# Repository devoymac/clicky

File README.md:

# Clicky

A portable, battery-powered heart-shaped "pet" in the style of STΛRBOY / Lil
Guy: a round animated eye, a personality driven by sensors, and a touch button
to pet it — it blushes when you give it affection. It runs on a single LiPo
battery and charges through the same USB-C port it uses to program.

## What it is

Clicky is a small companion you wear on your clothes or bag. Inside a
3D-printed heart lives a round screen that acts as its eye, and a set of
sensors give it a personality: it gets dizzy when you shake it, shivers when
it's cold, startles at loud noises, and falls asleep if you ignore it. Touch
it and it wakes up happy. It remembers its state across power-off.

## Design goals

- **Portable and battery-powered** — one small LiPo cell, no wall power.
- **Long battery life** — low-power sleeps, dimmed display when drowsy.
- **A living personality** — reacts to shake, cold, sound, and touch.
- **An original touch** — the heart blushes when you pet it.
- **Built by hand** — hand-wired to a tiny module, no complex PCB.

## Hardware

### Brain: Seeed XIAO ESP32-C3

A thumb-sized module with a built-in LiPo charger, WiFi/BLE, and plenty of
GPIOs, chosen over the nRF52840 for its lower cost and simplicity:

- **Built-in LiPo charger** — no external charging IC required. Plug in USB-C
  to charge; unplug to run on battery. Automatic.
- **WiFi + BLE** — headroom for a future phone companion or notifications.
- **USB-C** — programming and charging share the same port.
- **Low-power sleep** — dozes in µA range, waking on the touch button.

### The eye: GC9A01 1.28" round display

A 240x240 round SPI display that shows Clicky's expressions. Note: the
chosen module has no separate backlight pin — the backlight is tied to 3V3
internally, so the firmware should put the display to sleep instead of just
dimming it, to save battery when it dozes.

### The personality (sensors)

- **MPU-6000** (motion) — shake and tilt: dizzy, angry, look-downhill.
- **DS18B20** (temperature) — cold: shiver, then freeze with a blue tint.
- **MAX4466** (microphone amp) — loud sounds: startled, nervous.

### Interaction

- One tactile push button — pet the heart, it blushes and wakes up.

### Power

- A small certified LiPo (~320 mAh, e.g. 402535) with built-in protection,
  charged through the XIAO's own USB-C. Verify polarity before soldering
  (red = +, black = -).

## Schematic

The KiCad schematic is complete and validated by ERC. All nets are connected:
power (3V3/GND), I2C (MPU), 1-Wire (DS18B20 with 4.7k pull-up), SPI (display),
the microphone, the pet button, and the battery (VBAT). The remaining ERC
notices are intentional free pins and CLI false positives.

## PCB

## Wiring quick reference

- Battery + → XIAO VBAT ; battery - → GND (via JST-PH 2.0).
- Display GC9A01 (7-pin): VCC→3V3, GND→GND, SCL→D8 (SCK), SDA→D10 (MOSI),
  DC→D6, CS→D3, RST→3V3.
- MPU-6000 (I2C): VDD→3V3, GND→GND, SDA→D4, SCL→D5, AD0→GND, CPOUT→100nF
  to GND, REGOUT→100nF to GND.
- DS18B20: VDD→3V3, GND→GND, DQ→D7. R1 pulls DQ up to 3V3 (4.7k).
- Mic MAX4466: VCC→3V3, GND→GND, OUT→D1.
- Pet button: one pin→D0, other→GND.

## Firmware

Scaffolded for **Arduino IDE** in [`firmware/clicky/`](firmware/clicky/) — a
working skeleton that boots the GC9A01 eye and drives a mood state machine
(idle / dizzy / cold / startled / blush / sleep) from the MPU-6000, DS18B20,
mic and pet button. Compiles clean for the XIAO ESP32-C3 (27% flash).

Setup steps, board/library install and the TFT_eSPI GC9A01 config are in
[`firmware/SETUP-arduino-ide.md`](firmware/SETUP-arduino-ide.md).

## Bill of Materials

See [BOM.md](BOM.md) for the full parts list with prices (~$60 parts).

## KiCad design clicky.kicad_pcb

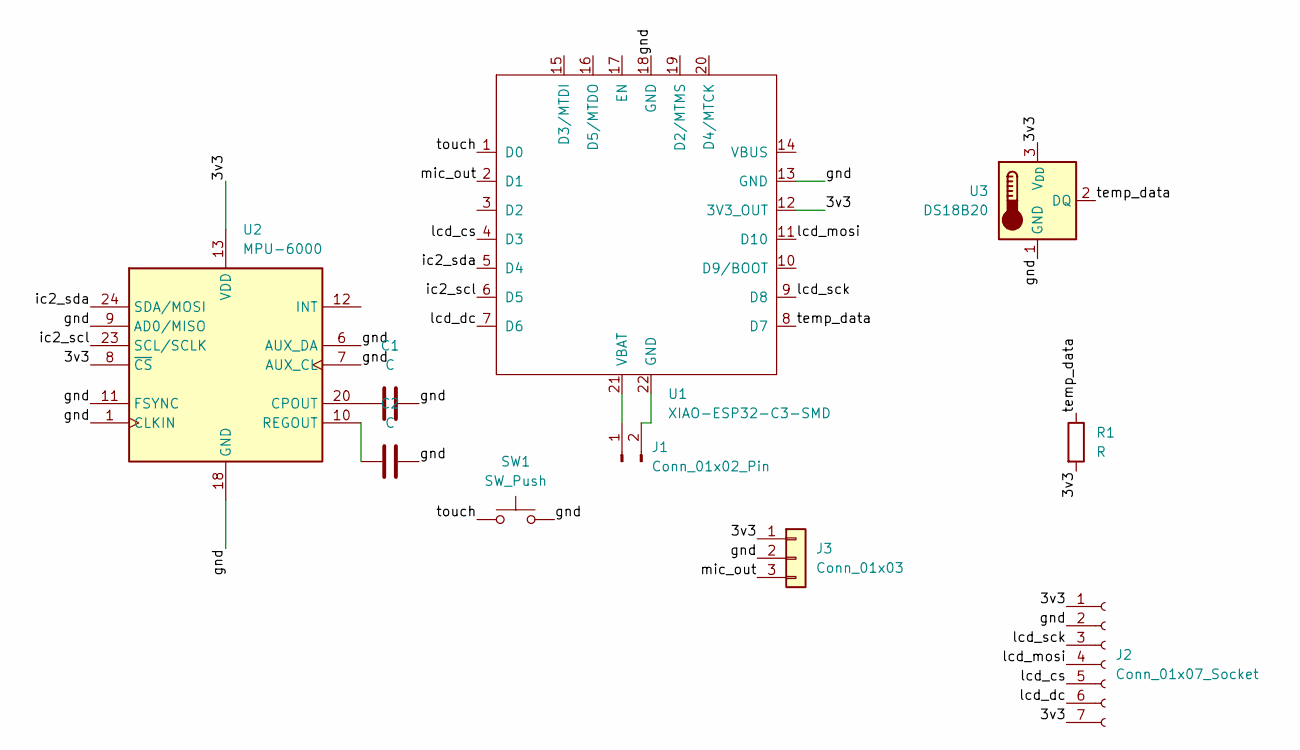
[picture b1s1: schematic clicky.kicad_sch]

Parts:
C1, C2: C; C_0603_1608Metric
J1: Conn_01x02_Pin; JST_PH_B2B-PH-K_1x02_P2.00mm_Vertical
J2: Conn_01x07_Socket; PinHeader_1x07_P2.54mm_Vertical
J3: Conn_01x03; PinHeader_1x03_P2.54mm_Vertical
R1: R; R_Axial_DIN0207_L6.3mm_D2.5mm_P10.16mm_Horizontal
SW1: SW_Push; SW_NKK_GW12LJP
U1: XIAO-ESP32-C3-SMD
U2: MPU-6000; InvenSense_QFN-24_4x4mm_P0.5mm
U3: DS18B20; TO-92_Inline

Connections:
/3v3: J2.1, J2.7, J3.1, R1.2, U1.12 (3V3_OUT), U2.8 (~CS), U2.13 (VDD), U3.3 (V_{DD})
/gnd: C1.1, C2.1, J2.2, J3.2, SW1.2, U1.13 (GND), U1.18 (GND), U2.1 (CLKIN), U2.6 (AUX_DA), U2.7 (AUX_CL), U2.9 (AD0/MISO), U2.11 (FSYNC), U2.18 (GND), U3.1 (GND)
/ic2_scl: U1.6 (D5), U2.23 (SCL/SCLK)
/ic2_sda: U1.5 (D4), U2.24 (SDA/MOSI)
/lcd_cs: J2.5, U1.4 (D3)
/lcd_dc: J2.6, U1.7 (D6)
/lcd_mosi: J2.4, U1.11 (D10)
/lcd_sck: J2.3, U1.9 (D8)
/mic_out: J3.3, U1.2 (D1)
/temp_data: R1.1, U1.8 (D7), U3.2 (DQ)
/touch: SW1.1, U1.1 (D0)
unnamed: J1.1, U1.21 (VBAT)
unnamed: J1.2, U1.22 (GND)
unnamed: C1.2, U2.20 (CPOUT)
unnamed: C2.2, U2.10 (REGOUT)

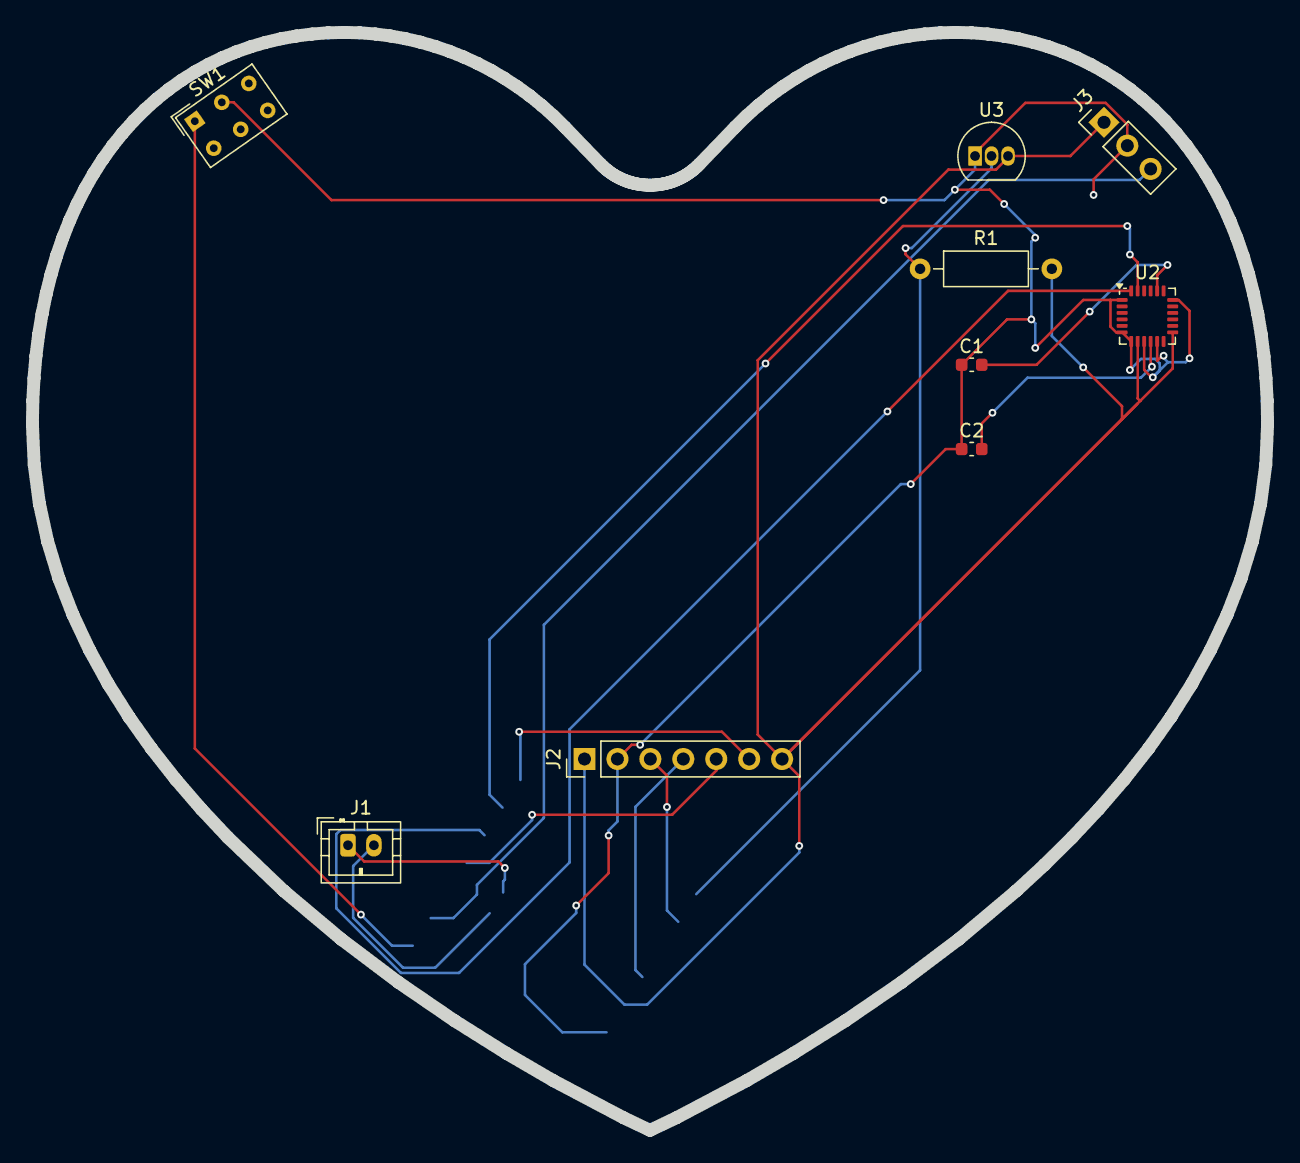
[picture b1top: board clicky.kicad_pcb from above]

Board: 2 copper layers, 95.2 x 84.7 mm, 10 parts (1 on the bottom side), 15 nets.

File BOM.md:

# Cliky – bill of materials

<!-- Generated by Half Life from project cmuur6jf409qe01smoq3ujl5z. Edits here are overwritten on the next sync. -->
<!-- Generated: 2026-10-09T20:39:36.242Z -->

> [!NOTE]
> This parts list is mirrored from [Half Life](https://halflife.hackclub.com). Editing it here will not change the platform's copy, and the next sync overwrites this file.

| Week | Tier | Parts funding |
| --- | --- | --- |
| Week 1 | Tier 2 | $65.00 |

| Part | What it's for | Qty | Unit | Total | Vendor |
| --- | --- | --- | --- | --- | --- |
| [XIAO-ESP32-C3-SMD](https://www.seeedstudio.com/Seeed-XIAO-ESP32C3-p-5431.html) | MCU with built-in LiPo charger and WiFi/BLE | 1 | $4.99 | $4.99 | [Seeed Studio](https://www.seeedstudio.com/Seeed-XIAO-ESP32C3-p-5431.html) |
| [MPU-6000](https://www.aliexpress.us/item/3256808332288788.html) | 6-axis accel/gyro (shake and tilt) | 1 | $1.88 | $1.88 | [InvenSense](https://www.aliexpress.us/item/3256808332288788.html) |
| [DS18B20](https://www.lcsc.com/product-detail/C376006.html) | Temperature sensor (cold detection) | 1 | $0.58 | $0.58 | [Maxim (UMW)](https://www.lcsc.com/product-detail/C376006.html) |
| [Conn_01x02_Pin](https://www.aliexpress.us/item/3256805611374476.html) | Battery connector (JST-PH 2.0) | 1 | $0.50 | $0.50 | [Generic](https://www.aliexpress.us/item/3256805611374476.html) |
| [GC9A01 1.28in round TFT (7-pin)](https://www.aliexpress.us/item/3256808098235758.html) | Round animated-eye display (240x240, SPI) | 1 | $4.48 | $4.48 | [GC9A01](https://www.aliexpress.us/item/3256808098235758.html) |
| [MAX4466 mic (3-pin)](https://www.aliexpress.us/item/3256805885526362.html) | Electret mic amplifier (sound detection) | 1 | $1.74 | $1.74 | [MAX4466](https://www.aliexpress.us/item/3256805885526362.html) |
| [4.7k](https://lcsc.com/product-detail/Carbon-Film-Resistors_4-7KR-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 | DS18B20 OneWire pull-up | 1 | $0.01 | $0.01 | [Generic](https://lcsc.com/product-detail/Carbon-Film-Resistors_4-7KR-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 |
| [100nF](https://www.aliexpress.us/item/3256807718543888.html) | MPU-6000 CPOUT decoupling | 1 | $0.05 | $0.05 | [Generic](https://www.aliexpress.us/item/3256807718543888.html) |
| [100nF](https://www.aliexpress.us/item/3256807718543888.html) | MPU-6000 REGOUT decoupling | 1 | $0.05 | $0.05 | [Generic](https://www.aliexpress.us/item/3256807718543888.html) |
| [SW_Push](https://www.aliexpress.us/item/3256807751442375.html) | Tactile pet/wake button | 1 | $0.10 | $0.10 | [Generic](https://www.aliexpress.us/item/3256807751442375.html) |
| [LiPo 402535 3.7V 320mAh](https://www.amazon.com/dp/B08215N9R8) | Battery cell (certified, with protection) | 1 | $9.99 | $9.99 | [EEMB](https://www.amazon.com/dp/B08215N9R8) |
| [30AWG silicone wire (5 colors)](https://www.aliexpress.us/item/3256808281675998.html) | Internal wiring | 1 | $6.96 | $6.96 | [Generic](https://www.aliexpress.us/item/3256808281675998.html) |
| [Prototype board 5x7cm 1.2mm](https://www.aliexpress.us/item/3256807718543888.html) | Solder modules onto (cut to circle) | 1 | $0.43 | $0.43 | [Generic](https://www.aliexpress.us/item/3256807718543888.html) |
| [PETG filament 1.75mm 1kg](https://www.aliexpress.us/item/3256812523172305.html) | 3D-printed heart shell | 1 | $14.81 | $14.81 | [Creality](https://www.aliexpress.us/item/3256812523172305.html) |
| [Plastic primer + chrome spray](https://www.amazon.com/dp/B003CT498U) | Chrome finish (optional) | 1 | $13.44 | $13.44 | [Rust-Oleum](https://www.amazon.com/dp/B003CT498U) |
| **Parts subtotal** | — | — | — | **$60.01** | — |
| **Tax & shipping** | — | — | — | **$0.00** | — |
| **Total** | — | — | — | **$60.01** | — |

$4.99 left of the tier's funding.
